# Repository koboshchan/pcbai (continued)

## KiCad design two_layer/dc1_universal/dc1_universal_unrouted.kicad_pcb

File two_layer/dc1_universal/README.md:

Universal DC1 hand-soldered card

This is one PCB design with four population variants. It replaces the repaired DC1a, DC1b, DC1c and DC1d weight cards, not DC0, DC2, DC3 or the motherboard. All existing boards remain unchanged.

The 100 × 100 mm outline, two 3.2 mm mounting holes and 76-pad straddle connector are copied from all four existing DC1 cards and mechanically checked for exact equality, including copper side, pad shape, size, position and drill. Put the L/arrow end at the motherboard socket's pin-1 end. The arrow is on both faces.

There are 532 resistor positions, all 0805 on the top face. The complete 64-input × 4-channel matrix has 256 logical weights and 512 separate positive/negative sign options. Twenty more positions cover feedback, both bias polarities and positive/negative ground balance on every channel. No weight position is omitted just because all four current models use zero there. The 112 added positions default to DNP in every current population. Existing references and positions are preserved. Future models use the same fixed 64-input/four-channel topology, supply rails and amplifier arrangement; different dimensions or circuit architectures need another board.

The left bank holds inputs 0–31 and the right bank holds inputs 32–63. Each row is an input and each bank has eight columns, positive then negative for local channels 0–3. Resistor centers have 5.2 mm column pitch and 2.65 mm row pitch. Local channels map to global neurons 0–3 on DC1a, 4–7 on DC1b, 8–11 on DC1c and 12–15 on DC1d. Connector pins A33–A36 carry local channel outputs 0–3; the motherboard slot determines the corresponding global neuron numbers. The other 72 contacts have the same roles in every variant.

Populate each board using only its matching DC1a.csv, DC1b.csv, DC1c.csv or DC1d.csv. POPULATION.md and population_chart.pdf show the same selections by physical row and column. DNP means leave the footprint empty, an open circuit. A zero weight is never a 0 Ω link. Do not populate both alternative sign positions unless the selected variant explicitly calls for them.

DC1a uses 191 resistors, DC1b 230, DC1c 181 and DC1d 141. Every variant also uses one TL074 SOIC-14, two 100 nF 50 V 0805 rail-decoupling capacitors and the manually soldered 2 × 38 straddle header. Eight resistors on each variant require 1% tolerance; the other populated resistors use the recorded 5% tolerance. CSV values and net pairs are checked against both the source boards and their physical differential-repair manifest. The source board hashes are retained in manifest.json. These selections preserve the trained network; no retraining was performed.

Routing of the 532-site board is in progress. The generated seed has zero DRC errors, 134 unconnected route items and six library-lookup warnings. No routed 532-site candidate has passed release verification yet. The previous 420-site candidate is archived outside this folder and is not a release of this design. This is a two-layer design with minimum 0.2 mm tracks, 0.2 mm clearance and 0.6/0.3 mm vias. No DRC exclusions were added. No board has been ordered or fabricated, and publication is awaiting approval.

Rebuild from this directory using /usr/bin/python3 build.py. Exported Specctra dc1_universal.dsn retains deliberately pre-routed front vertical summing buses and rear input rows, with vias connecting the input resistor pads. Complete the remaining connections with FreeRouting, save dc1_universal.ses, and run /usr/bin/python3 finish.py. Finish refuses release if any DRC error or unconnected item remains. Run population_chart.py to regenerate the solder chart.

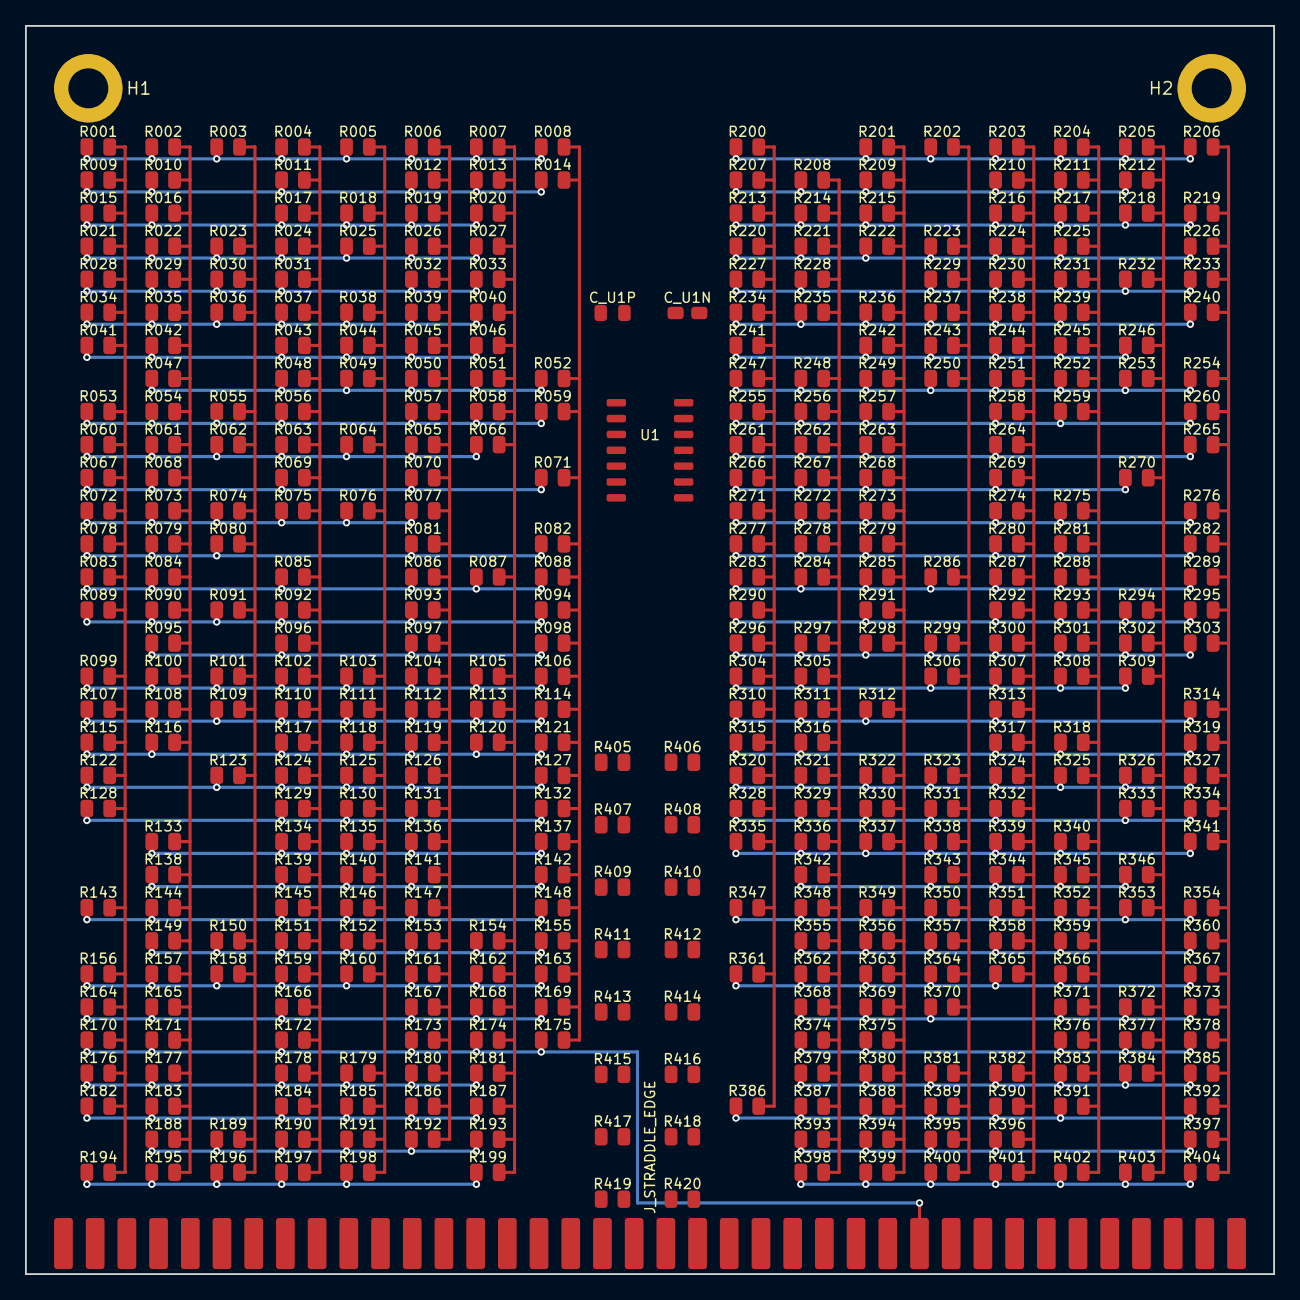
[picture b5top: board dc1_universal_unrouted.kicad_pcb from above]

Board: 2 copper layers, 100.0 x 100.0 mm, 426 parts (0 on the bottom side), 80 nets.

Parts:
C_U1N, C_U1P: 0.1uF; C_0805_2012Metric
H1, H2: MountingHole; MountingHole_3.2mm_M3_Pad
J_STRADDLE_EDGE: PinHeader_2x38_Straddle; PinHeader_2x38_Straddle_P2.54mm
R001, R002, R003, R004, R005, R006, R007, R008, R009, R010, R011, R012, R013, R014, R015, R016, R017, R018, R019, R020, R021, R022, R023, R024, R025, R026, R027, R028, R029, R030, R031, R032, R033, R034, R035, R036, R037, R038, R039, R040, R041, R042, R043, R044, R045, R046, R047, R048, R049, R050, R051, R052, R053, R054, R055, R056, R057, R058, R059, R060, R061, R062, R063, R064, R065, R066, R067, R068, R069, R070, R071, R072, R073, R074, R075, R076, R077, R078, R079, R080, R081, R082, R083, R084, R085, R086, R087, R088, R089, R090, R091, R092, R093, R094, R095, R096, R097, R098, R099, R100, R101, R102, R103, R104, R105, R106, R107, R108, R109, R110, R111, R112, R113, R114, R115, R116, R117, R118, R119, R120, R121, R122, R123, R124, R125, R126, R127, R128, R129, R130, R131, R132, R133, R134, R135, R136, R137, R138, R139, R140, R141, R142, R143, R144, R145, R146, R147, R148, R149, R150, R151, R152, R153, R154, R155, R156, R157, R158, R159, R160, R161, R162, R163, R164, R165, R166, R167, R168, R169, R170, R171, R172, R173, R174, R175, R176, R177, R178, R179, R180, R181, R182, R183, R184, R185, R186, R187, R188, R189, R190, R191, R192, R193, R194, R195, R196, R197, R198, R199, R200, R201, R202, R203, R204, R205, R206, R207, R208, R209, R210, R211, R212, R213, R214, R215, R216, R217, R218, R219, R220, R221, R222, R223, R224, R225, R226, R227, R228, R229, R230, R231, R232, R233, R234, R235, R236, R237, R238, R239, R240, R241, R242, R243, R244, R245, R246, R247, R248, R249, R250, R251, R252, R253, R254, R255, R256, R257, R258, R259, R260, R261, R262, R263, R264, R265, R266, R267, R268, R269, R270, R271, R272, R273, R274, R275, R276, R277, R278, R279, R280, R281, R282, R283, R284, R285, R286, R287, R288, R289, R290, R291, R292, R293, R294, R295, R296, R297, R298, R299, R300, R301, R302, R303, R304, R305, R306, R307, R308, R309, R310, R311, R312, R313, R314, R315, R316, R317, R318, R319, R320, R321, R322, R323, R324, R325, R326, R327, R328, R329, R330, R331, R332, R333, R334, R335, R336, R337, R338, R339, R340, R341, R342, R343, R344, R345, R346, R347, R348, R349, R350, R351, R352, R353, R354, R355, R356, R357, R358, R359, R360, R361, R362, R363, R364, R365, R366, R367, R368, R369, R370, R371, R372, R373, R374, R375, R376, R377, R378, R379, R380, R381, R382, R383, R384, R385, R386, R387, R388, R389, R390, R391, R392, R393, R394, R395, R396, R397, R398, R399, R400, R401, R402, R403, R404, R405, R406, R407, R408, R409, R410, R411, R412, R413, R414, R415, R416, R417, R418, R419, R420: POPULATION; R_0805_2012Metric
U1: TL074; SOIC-14_3.9x8.7mm_P1.27mm

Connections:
+5V_REF: J_STRADDLE_EDGE.B35, R405.1, R406.1, R407.1, R408.1, R409.1
+15V: C_U1P.2, J_STRADDLE_EDGE.B33, J_STRADDLE_EDGE.B34, U1.4
-15V: C_U1N.1, J_STRADDLE_EDGE.B37, J_STRADDLE_EDGE.B38, U1.11
GND: C_U1N.2, C_U1P.1, H1.1, H2.1, J_STRADDLE_EDGE.A37, J_STRADDLE_EDGE.A38, R410.1, R411.1, R412.1, R413.1, R414.1, R415.1, R416.1
INV_N0: R002.2, R010.2, R016.2, R022.2, R029.2, R035.2, R042.2, R047.2, R054.2, R061.2, R068.2, R073.2, R079.2, R084.2, R090.2, R095.2, R100.2, R108.2, R116.2, R133.2, R138.2, R144.2, R149.2, R157.2, R165.2, R171.2, R177.2, R183.2, R188.2, R195.2, R208.2, R214.2, R221.2, R228.2, R235.2, R248.2, R256.2, R262.2, R267.2, R272.2, R278.2, R284.2, R297.2, R305.2, R311.2, R316.2, R321.2, R329.2, R336.2, R342.2, R348.2, R355.2, R362.2, R368.2, R374.2, R379.2, R387.2, R393.2, R398.2, R405.2, R417.1, U1.2
INV_N1: R004.2, R011.2, R017.2, R024.2, R031.2, R037.2, R043.2, R048.2, R056.2, R063.2, R069.2, R075.2, R085.2, R092.2, R096.2, R102.2, R110.2, R117.2, R124.2, R129.2, R134.2, R139.2, R145.2, R151.2, R159.2, R166.2, R172.2, R178.2, R184.2, R190.2, R197.2, R202.2, R223.2, R229.2, R237.2, R243.2, R250.2, R286.2, R299.2, R306.2, R323.2, R331.2, R338.2, R343.2, R350.2, R357.2, R364.2, R370.2, R381.2, R389.2, R395.2, R400.2, R406.2, R410.2, R418.1, U1.6
INV_N2: R006.2, R012.2, R019.2, R026.2, R032.2, R039.2, R045.2, R050.2, R057.2, R065.2, R070.2, R077.2, R081.2, R086.2, R093.2, R097.2, R104.2, R112.2, R119.2, R126.2, R131.2, R136.2, R141.2, R147.2, R153.2, R161.2, R167.2, R173.2, R180.2, R186.2, R192.2, R204.2, R211.2, R217.2, R225.2, R231.2, R239.2, R245.2, R252.2, R259.2, R275.2, R281.2, R288.2, R293.2, R301.2, R308.2, R318.2, R325.2, R340.2, R345.2, R352.2, R359.2, R366.2, R371.2, R376.2, R383.2, R391.2, R402.2, R407.2, R411.2, R419.1, U1.9
INV_N3: R008.2, R014.2, R052.2, R059.2, R071.2, R082.2, R088.2, R094.2, R098.2, R106.2, R114.2, R121.2, R127.2, R132.2, R137.2, R142.2, R148.2, R155.2, R163.2, R169.2, R175.2, R206.2, R219.2, R226.2, R233.2, R240.2, R254.2, R260.2, R265.2, R276.2, R282.2, R289.2, R295.2, R303.2, R314.2, R319.2, R327.2, R334.2, R341.2, R354.2, R360.2, R367.2, R373.2, R378.2, R385.2, R392.2, R397.2, R404.2, R408.2, R412.2, R420.1, U1.13
IN_0: J_STRADDLE_EDGE.A1, R001.1, R002.1, R003.1, R004.1, R005.1, R006.1, R007.1, R008.1
IN_1: J_STRADDLE_EDGE.A2, R009.1, R010.1, R011.1, R012.1, R013.1, R014.1
IN_2: J_STRADDLE_EDGE.A3, R015.1, R016.1, R017.1, R018.1, R019.1, R020.1
IN_3: J_STRADDLE_EDGE.A4, R021.1, R022.1, R023.1, R024.1, R025.1, R026.1, R027.1
IN_4: J_STRADDLE_EDGE.A5, R028.1, R029.1, R030.1, R031.1, R032.1, R033.1
IN_5: J_STRADDLE_EDGE.A6, R034.1, R035.1, R036.1, R037.1, R038.1, R039.1, R040.1
IN_6: J_STRADDLE_EDGE.A7, R041.1, R042.1, R043.1, R044.1, R045.1, R046.1
IN_7: J_STRADDLE_EDGE.A8, R047.1, R048.1, R049.1, R050.1, R051.1, R052.1
IN_8: J_STRADDLE_EDGE.A9, R053.1, R054.1, R055.1, R056.1, R057.1, R058.1, R059.1
IN_9: J_STRADDLE_EDGE.A10, R060.1, R061.1, R062.1, R063.1, R064.1, R065.1, R066.1
IN_10: J_STRADDLE_EDGE.A11, R067.1, R068.1, R069.1, R070.1, R071.1
IN_11: J_STRADDLE_EDGE.A12, R072.1, R073.1, R074.1, R075.1, R076.1, R077.1
IN_12: J_STRADDLE_EDGE.A13, R078.1, R079.1, R080.1, R081.1, R082.1
IN_13: J_STRADDLE_EDGE.A14, R083.1, R084.1, R085.1, R086.1, R087.1, R088.1
IN_14: J_STRADDLE_EDGE.A15, R089.1, R090.1, R091.1, R092.1, R093.1, R094.1
IN_15: J_STRADDLE_EDGE.A16, R095.1, R096.1, R097.1, R098.1
IN_16: J_STRADDLE_EDGE.A17, R099.1, R100.1, R101.1, R102.1, R103.1, R104.1, R105.1, R106.1
IN_17: J_STRADDLE_EDGE.A18, R107.1, R108.1, R109.1, R110.1, R111.1, R112.1, R113.1, R114.1
IN_18: J_STRADDLE_EDGE.A19, R115.1, R116.1, R117.1, R118.1, R119.1, R120.1, R121.1
IN_19: J_STRADDLE_EDGE.A20, R122.1, R123.1, R124.1, R125.1, R126.1, R127.1
IN_20: J_STRADDLE_EDGE.A21, R128.1, R129.1, R130.1, R131.1, R132.1
IN_21: J_STRADDLE_EDGE.A22, R133.1, R134.1, R135.1, R136.1, R137.1
IN_22: J_STRADDLE_EDGE.A23, R138.1, R139.1, R140.1, R141.1, R142.1
IN_23: J_STRADDLE_EDGE.A24, R143.1, R144.1, R145.1, R146.1, R147.1, R148.1
IN_24: J_STRADDLE_EDGE.A25, R149.1, R150.1, R151.1, R152.1, R153.1, R154.1, R155.1
IN_25: J_STRADDLE_EDGE.A26, R156.1, R157.1, R158.1, R159.1, R160.1, R161.1, R162.1, R163.1
IN_26: J_STRADDLE_EDGE.A27, R164.1, R165.1, R166.1, R167.1, R168.1, R169.1
IN_27: J_STRADDLE_EDGE.A28, R170.1, R171.1, R172.1, R173.1, R174.1, R175.1
IN_28: J_STRADDLE_EDGE.A29, R176.1, R177.1, R178.1, R179.1, R180.1, R181.1
IN_29: J_STRADDLE_EDGE.A30, R182.1, R183.1, R184.1, R185.1, R186.1, R187.1
IN_30: J_STRADDLE_EDGE.A31, R188.1, R189.1, R190.1, R191.1, R192.1, R193.1
IN_31: J_STRADDLE_EDGE.A32, R194.1, R195.1, R196.1, R197.1, R198.1, R199.1
IN_32: J_STRADDLE_EDGE.B1, R200.1, R201.1, R202.1, R203.1, R204.1, R205.1, R206.1
IN_33: J_STRADDLE_EDGE.B2, R207.1, R208.1, R209.1, R210.1, R211.1, R212.1
IN_34: J_STRADDLE_EDGE.B3, R213.1, R214.1, R215.1, R216.1, R217.1, R218.1, R219.1
IN_35: J_STRADDLE_EDGE.B4, R220.1, R221.1, R222.1, R223.1, R224.1, R225.1, R226.1
IN_36: J_STRADDLE_EDGE.B5, R227.1, R228.1, R229.1, R230.1, R231.1, R232.1, R233.1
IN_37: J_STRADDLE_EDGE.B6, R234.1, R235.1, R236.1, R237.1, R238.1, R239.1, R240.1
IN_38: J_STRADDLE_EDGE.B7, R241.1, R242.1, R243.1, R244.1, R245.1, R246.1
IN_39: J_STRADDLE_EDGE.B8, R247.1, R248.1, R249.1, R250.1, R251.1, R252.1, R253.1, R254.1
IN_40: J_STRADDLE_EDGE.B9, R255.1, R256.1, R257.1, R258.1, R259.1, R260.1
IN_41: J_STRADDLE_EDGE.B10, R261.1, R262.1, R263.1, R264.1, R265.1
IN_42: J_STRADDLE_EDGE.B11, R266.1, R267.1, R268.1, R269.1, R270.1
IN_43: J_STRADDLE_EDGE.B12, R271.1, R272.1, R273.1, R274.1, R275.1, R276.1
IN_44: J_STRADDLE_EDGE.B13, R277.1, R278.1, R279.1, R280.1, R281.1, R282.1
IN_45: J_STRADDLE_EDGE.B14, R283.1, R284.1, R285.1, R286.1, R287.1, R288.1, R289.1
IN_46: J_STRADDLE_EDGE.B15, R290.1, R291.1, R292.1, R293.1, R294.1, R295.1
IN_47: J_STRADDLE_EDGE.B16, R296.1, R297.1, R298.1, R299.1, R300.1, R301.1, R302.1, R303.1
IN_48: J_STRADDLE_EDGE.B17, R304.1, R305.1, R306.1, R307.1, R308.1, R309.1
IN_49: J_STRADDLE_EDGE.B18, R310.1, R311.1, R312.1, R313.1, R314.1
IN_50: J_STRADDLE_EDGE.B19, R315.1, R316.1, R317.1, R318.1, R319.1
IN_51: J_STRADDLE_EDGE.B20, R320.1, R321.1, R322.1, R323.1, R324.1, R325.1, R326.1, R327.1
IN_52: J_STRADDLE_EDGE.B21, R328.1, R329.1, R330.1, R331.1, R332.1, R333.1, R334.1
IN_53: J_STRADDLE_EDGE.B22, R335.1, R336.1, R337.1, R338.1, R339.1, R340.1, R341.1
IN_54: J_STRADDLE_EDGE.B23, R342.1, R343.1, R344.1, R345.1, R346.1
IN_55: J_STRADDLE_EDGE.B24, R347.1, R348.1, R349.1, R350.1, R351.1, R352.1, R353.1, R354.1
IN_56: J_STRADDLE_EDGE.B25, R355.1, R356.1, R357.1, R358.1, R359.1, R360.1
IN_57: J_STRADDLE_EDGE.B26, R361.1, R362.1, R363.1, R364.1, R365.1, R366.1, R367.1
IN_58: J_STRADDLE_EDGE.B27, R368.1, R369.1, R370.1, R371.1, R372.1, R373.1
IN_59: J_STRADDLE_EDGE.B28, R374.1, R375.1, R376.1, R377.1, R378.1
IN_60: J_STRADDLE_EDGE.B29, R379.1, R380.1, R381.1, R382.1, R383.1, R384.1, R385.1
IN_61: J_STRADDLE_EDGE.B30, R386.1, R387.1, R388.1, R389.1, R390.1, R391.1, R392.1
IN_62: J_STRADDLE_EDGE.B31, R393.1, R394.1, R395.1, R396.1, R397.1
IN_63: J_STRADDLE_EDGE.B32, R398.1, R399.1, R400.1, R401.1, R402.1, R403.1, R404.1
POS_N0: R001.2, R009.2, R015.2, R021.2, R028.2, R034.2, R041.2, R053.2, R060.2, R067.2, R072.2, R078.2, R083.2, R089.2, R099.2, R107.2, R115.2, R122.2, R128.2, R143.2, R156.2, R164.2, R170.2, R176.2, R182.2, R194.2, R200.2, R207.2, R213.2, R220.2, R227.2, R234.2, R241.2, R247.2, R255.2, R261.2, R266.2, R271.2, R277.2, R283.2, R290.2, R296.2, R304.2, R310.2, R315.2, R320.2, R328.2, R335.2, R347.2, R361.2, R386.2, R413.2, U1.3
POS_N1: R003.2, R023.2, R030.2, R036.2, R055.2, R062.2, R074.2, R080.2, R091.2, R101.2, R109.2, R123.2, R150.2, R158.2, R189.2, R196.2, R201.2, R209.2, R215.2, R222.2, R236.2, R242.2, R249.2, R257.2, R263.2, R268.2, R273.2, R279.2, R285.2, R291.2, R298.2, R312.2, R322.2, R330.2, R337.2, R349.2, R356.2, R363.2, R369.2, R375.2, R380.2, R388.2, R394.2, R399.2, R414.2, U1.5
POS_N2: R005.2, R018.2, R025.2, R038.2, R044.2, R049.2, R064.2, R076.2, R103.2, R111.2, R118.2, R125.2, R130.2, R135.2, R140.2, R146.2, R152.2, R160.2, R179.2, R185.2, R191.2, R198.2, R203.2, R210.2, R216.2, R224.2, R230.2, R238.2, R244.2, R251.2, R258.2, R264.2, R269.2, R274.2, R280.2, R287.2, R292.2, R300.2, R307.2, R313.2, R317.2, R324.2, R332.2, R339.2, R344.2, R351.2, R358.2, R365.2, R382.2, R390.2, R396.2, R401.2, R409.2, R415.2, U1.10
POS_N3: R007.2, R013.2, R020.2, R027.2, R033.2, R040.2, R046.2, R051.2, R058.2, R066.2, R087.2, R105.2, R113.2, R120.2, R154.2, R162.2, R168.2, R174.2, R181.2, R187.2, R193.2, R199.2, R205.2, R212.2, R218.2, R232.2, R246.2, R253.2, R270.2, R294.2, R302.2, R309.2, R326.2, R333.2, R346.2, R353.2, R372.2, R377.2, R384.2, R403.2, R416.2, U1.12
V_SUM_0: J_STRADDLE_EDGE.A33, R417.2, U1.1
V_SUM_1: J_STRADDLE_EDGE.A34, R418.2, U1.7
V_SUM_2: J_STRADDLE_EDGE.A35, R419.2, U1.8
V_SUM_3: J_STRADDLE_EDGE.A36, R420.2, U1.14

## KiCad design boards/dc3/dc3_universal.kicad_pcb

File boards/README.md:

Current paid v2 board sources and matching fabrication ZIPs live here. PCB bytes are preserved exactly; SHA256.json records source and ZIP hashes. DC1 is the four-layer universal design. Populate four copies using DC1a.csv through DC1d.csv and POPULATION.md. ADS carrier is the current v3 targeted design.

The motherboard requires a bottom bodge wire connecting JS1 B7 at (18.25, 44.27) mm to JS2 B7 at (18.25, 55.27) mm. Fit it before powering the stack.

Only existing matching project/rule files were copied. DC2 and the motherboard final source folders did not contain matching project files. Custom footprints and 3D models are retained at the repository root. Some immutable boards embed the original /Users/lucaszhang/pcbai/3dmodels paths; on other machines provide that path as a symlink or remap models in a separate working copy. Do not edit the release sources just to change model paths.

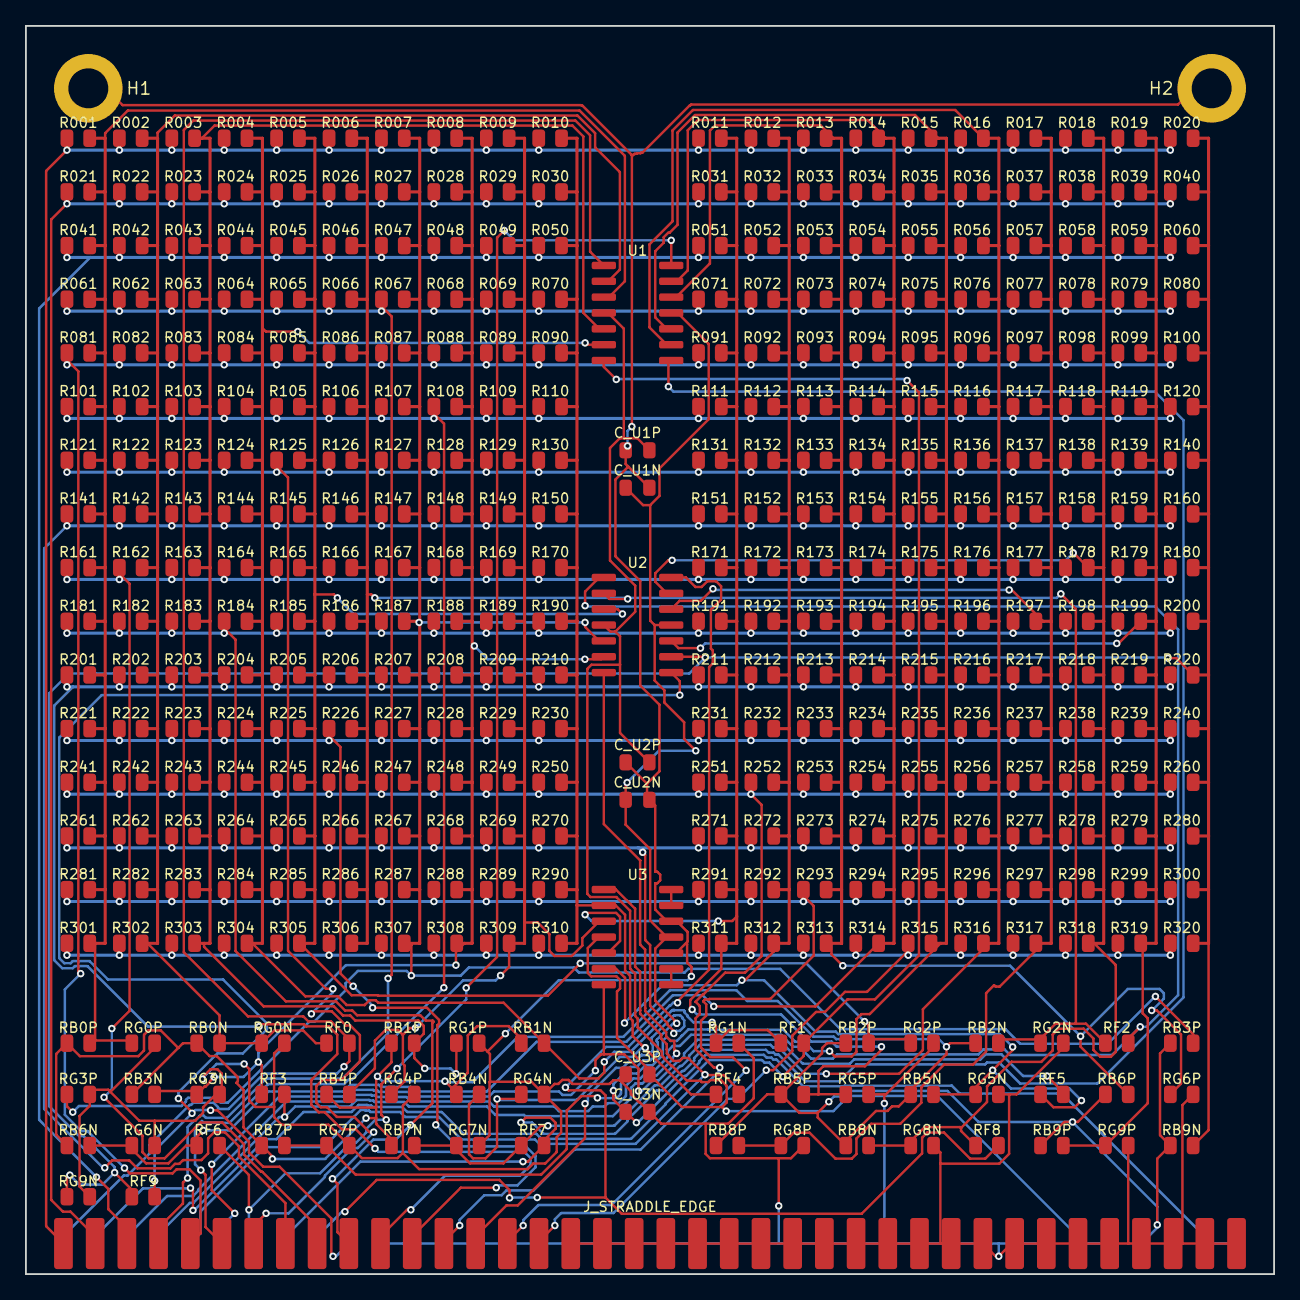
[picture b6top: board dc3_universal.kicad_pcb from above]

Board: 2 copper layers, 100.0 x 100.0 mm, 382 parts (0 on the bottom side), 52 nets.

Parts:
C_U1N, C_U1P, C_U2N, C_U2P, C_U3N, C_U3P: 0.1uF; C_0805_2012Metric
H1, H2: MountingHole; MountingHole_3.2mm_M3_Pad
J_STRADDLE_EDGE: PinHeader_2x38_Straddle; PinHeader_2x38_Straddle_P2.54mm
R001, R004, R005, R008, R009, R011, R013, R016, R017, R020, R022, R023, R024, R025, R026, R027, R029, R030, R031, R033, R034, R035, R036, R037, R038, R039, R042, R043, R045, R048, R049, R052, R053, R055, R058, R059, R060, R061, R063, R066, R068, R069, R071, R073, R076, R077, R079, R081, R084, R086, R087, R089, R092, R093, R096, R097, R099, R101, R104, R105, R108, R110, R111, R113, R115, R117, R118, R120, R121, R123, R125, R127, R128, R129, R132, R134, R135, R137, R138, R139, R141, R143, R144, R145, R148, R149, R152, R154, R155, R157, R158, R159, R162, R163, R165, R167, R169, R171, R172, R173, R176, R178, R180, R181, R184, R185, R187, R190, R192, R194, R196, R197, R199, R201, R202, R203, R206, R208, R209, R211, R213, R216, R217, R219, R221, R222, R223, R224, R225, R226, R227, R228, R230, R231, R233, R235, R236, R237, R238, R239, R240, R241, R243, R246, R247, R250, R251, R254, R255, R257, R258, R259, R261, R264, R265, R266, R267, R268, R270, R271, R273, R274, R275, R276, R277, R278, R279, R280, R281, R283, R286, R287, R288, R290, R292, R293, R296, R297, R300, R301, R302, R304, R305, R306, R307, R308, R309, R310, R311, R313, R315, R316, R317, R318, R319, R320: DNP; R_0805_2012Metric
R002, R065, R168, R183, R214: 91k; R_0805_2012Metric
R003, R062, R131, R150, R182, R284: 100k; R_0805_2012Metric
R006: 1.6M; R_0805_2012Metric
R007, R028, R109, R126, R153, R212, R218, R262, R282: 220k; R_0805_2012Metric
R010, R056, R107, R147, R174, R188, R272: 270k; R_0805_2012Metric
R012, R014, R102: 56k; R_0805_2012Metric
R015, R072: 470k; R_0805_2012Metric
R018, R040, R112, R119, R186, R189, R198, R215, R229, R234, R253: 180k; R_0805_2012Metric
R019, R046, R091, R094, R179, R252, R299: 300k; R_0805_2012Metric
R021, R047, R050, R161, R207, R232, R295, R312: 240k; R_0805_2012Metric
R032, R103: 82k; R_0805_2012Metric
R041, R220, R298: 110k; R_0805_2012Metric
R044: 51k; R_0805_2012Metric
R051, R067, R075, R314: 360k; R_0805_2012Metric
R054, R100: 430k; R_0805_2012Metric
R057: 5.1M; R_0805_2012Metric
R064, R140, R156, R200, R205, R269: 150k; R_0805_2012Metric
R070, R080, R106, R289: 130k; R_0805_2012Metric
R074, R114, R130, R146, R151, R204: 68k; R_0805_2012Metric
R078, R116, R122, R133, R166, R244, R249, R294: 200k; R_0805_2012Metric
R082, R191: 1M; R_0805_2012Metric
R083, R090, R177: 120k; R_0805_2012Metric
R085: 680k; R_0805_2012Metric
R088, R285: 750k; R_0805_2012Metric
R095, R248: 390k; R_0805_2012Metric
R098: 62k; R_0805_2012Metric
R124, R256: 43k; R_0805_2012Metric
R136, R175: 330k; R_0805_2012Metric
R142, R160: 75k; R_0805_2012Metric
R164, R260, R303: 160k; R_0805_2012Metric
R170, R193, R195: 620k; R_0805_2012Metric
R210: 33k; R_0805_2012Metric
R242: 510k; R_0805_2012Metric
R245: 1.1M; R_0805_2012Metric
R263: 820k; R_0805_2012Metric
R291: 2.7M; R_0805_2012Metric
RB0N, RB1N, RB2N, RB3P, RB4P, RB5P, RB6N, RB7N, RB8N, RB8P, RB9P: DNP; R_0805_2012Metric
RB0P: 270k; R_0805_2012Metric
RB1P, RB3N: 160k; R_0805_2012Metric
RB2P, RB4N: 560k; R_0805_2012Metric
RB5N: 2M; R_0805_2012Metric
RB6P: 240k; R_0805_2012Metric
RB7P: 3.9M; R_0805_2012Metric
RB9N: 360k; R_0805_2012Metric
RF0, RF1, RF2, RF3, RF4, RF5, RF6, RF7, RF8, RF9: 100k; R_0805_2012Metric
RG0N, RG1N, RG2N, RG3N, RG4N, RG5N, RG6N, RG7N, RG8N, RG9N: DNP; R_0805_2012Metric
RG0P: 14.7k; R_0805_2012Metric
RG1P: 24.9k; R_0805_2012Metric
RG2P: 35.7k; R_0805_2012Metric
RG3P: 61.9k; R_0805_2012Metric
RG4P: 17.4k; R_0805_2012Metric
RG5P: 28k; R_0805_2012Metric
RG6P: 14.3k; R_0805_2012Metric
RG7P: 34k; R_0805_2012Metric
RG8P: 21k; R_0805_2012Metric
RG9P: 18.2k; R_0805_2012Metric
U1, U2, U3: TL074; SOIC-14_3.9x8.7mm_P1.27mm

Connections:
+5V_REF: J_STRADDLE_EDGE.B35, RB0N.1, RB0P.1, RB1N.1, RB1P.1, RB2N.1, RB2P.1, RB3N.1, RB3P.1, RB4N.1, RB4P.1, RB5N.1, RB5P.1, RB6N.1, RB6P.1, RB7N.1, RB7P.1, RB8N.1, RB8P.1, RB9N.1, RB9P.1
+15V: C_U1P.2, C_U2P.2, C_U3P.2, J_STRADDLE_EDGE.B33, J_STRADDLE_EDGE.B34, U1.4, U2.4, U3.4
-15V: C_U1N.1, C_U2N.1, C_U3N.1, J_STRADDLE_EDGE.B37, J_STRADDLE_EDGE.B38, U1.11, U2.11, U3.11
ACT_0: J_STRADDLE_EDGE.A1, R001.1, R002.1, R003.1, R004.1, R005.1, R006.1, R007.1, R008.1, R009.1, R010.1, R011.1, R012.1, R013.1, R014.1, R015.1, R016.1, R017.1, R018.1, R019.1, R020.1
ACT_1: J_STRADDLE_EDGE.A2, R021.1, R022.1, R023.1, R024.1, R025.1, R026.1, R027.1, R028.1, R029.1, R030.1, R031.1, R032.1, R033.1, R034.1, R035.1, R036.1, R037.1, R038.1, R039.1, R040.1
ACT_2: J_STRADDLE_EDGE.A3, R041.1, R042.1, R043.1, R044.1, R045.1, R046.1, R047.1, R048.1, R049.1, R050.1, R051.1, R052.1, R053.1, R054.1, R055.1, R056.1, R057.1, R058.1, R059.1, R060.1
ACT_3: J_STRADDLE_EDGE.A4, R061.1, R062.1, R063.1, R064.1, R065.1, R066.1, R067.1, R068.1, R069.1, R070.1, R071.1, R072.1, R073.1, R074.1, R075.1, R076.1, R077.1, R078.1, R079.1, R080.1
ACT_4: J_STRADDLE_EDGE.A5, R081.1, R082.1, R083.1, R084.1, R085.1, R086.1, R087.1, R088.1, R089.1, R090.1, R091.1, R092.1, R093.1, R094.1, R095.1, R096.1, R097.1, R098.1, R099.1, R100.1
ACT_5: J_STRADDLE_EDGE.A6, R101.1, R102.1, R103.1, R104.1, R105.1, R106.1, R107.1, R108.1, R109.1, R110.1, R111.1, R112.1, R113.1, R114.1, R115.1, R116.1, R117.1, R118.1, R119.1, R120.1
ACT_6: J_STRADDLE_EDGE.A7, R121.1, R122.1, R123.1, R124.1, R125.1, R126.1, R127.1, R128.1, R129.1, R130.1, R131.1, R132.1, R133.1, R134.1, R135.1, R136.1, R137.1, R138.1, R139.1, R140.1
ACT_7: J_STRADDLE_EDGE.A8, R141.1, R142.1, R143.1, R144.1, R145.1, R146.1, R147.1, R148.1, R149.1, R150.1, R151.1, R152.1, R153.1, R154.1, R155.1, R156.1, R157.1, R158.1, R159.1, R160.1
ACT_8: J_STRADDLE_EDGE.A9, R161.1, R162.1, R163.1, R164.1, R165.1, R166.1, R167.1, R168.1, R169.1, R170.1, R171.1, R172.1, R173.1, R174.1, R175.1, R176.1, R177.1, R178.1, R179.1, R180.1
ACT_9: J_STRADDLE_EDGE.A10, R181.1, R182.1, R183.1, R184.1, R185.1, R186.1, R187.1, R188.1, R189.1, R190.1, R191.1, R192.1, R193.1, R194.1, R195.1, R196.1, R197.1, R198.1, R199.1, R200.1
ACT_10: J_STRADDLE_EDGE.A11, R201.1, R202.1, R203.1, R204.1, R205.1, R206.1, R207.1, R208.1, R209.1, R210.1, R211.1, R212.1, R213.1, R214.1, R215.1, R216.1, R217.1, R218.1, R219.1, R220.1
ACT_11: J_STRADDLE_EDGE.A12, R221.1, R222.1, R223.1, R224.1, R225.1, R226.1, R227.1, R228.1, R229.1, R230.1, R231.1, R232.1, R233.1, R234.1, R235.1, R236.1, R237.1, R238.1, R239.1, R240.1
ACT_12: J_STRADDLE_EDGE.A13, R241.1, R242.1, R243.1, R244.1, R245.1, R246.1, R247.1, R248.1, R249.1, R250.1, R251.1, R252.1, R253.1, R254.1, R255.1, R256.1, R257.1, R258.1, R259.1, R260.1
ACT_13: J_STRADDLE_EDGE.A14, R261.1, R262.1, R263.1, R264.1, R265.1, R266.1, R267.1, R268.1, R269.1, R270.1, R271.1, R272.1, R273.1, R274.1, R275.1, R276.1, R277.1, R278.1, R279.1, R280.1
ACT_14: J_STRADDLE_EDGE.A15, R281.1, R282.1, R283.1, R284.1, R285.1, R286.1, R287.1, R288.1, R289.1, R290.1, R291.1, R292.1, R293.1, R294.1, R295.1, R296.1, R297.1, R298.1, R299.1, R300.1
ACT_15: J_STRADDLE_EDGE.A16, R301.1, R302.1, R303.1, R304.1, R305.1, R306.1, R307.1, R308.1, R309.1, R310.1, R311.1, R312.1, R313.1, R314.1, R315.1, R316.1, R317.1, R318.1, R319.1, R320.1
GND: C_U1N.2, C_U1P.1, C_U2N.2, C_U2P.1, C_U3N.2, C_U3P.1, H1.1, H2.1, J_STRADDLE_EDGE.A17, J_STRADDLE_EDGE.A18, J_STRADDLE_EDGE.A19, J_STRADDLE_EDGE.A20, J_STRADDLE_EDGE.A21, J_STRADDLE_EDGE.A22, J_STRADDLE_EDGE.A23, J_STRADDLE_EDGE.A24, J_STRADDLE_EDGE.A25, J_STRADDLE_EDGE.A26, J_STRADDLE_EDGE.A27, J_STRADDLE_EDGE.A28, J_STRADDLE_EDGE.A29, J_STRADDLE_EDGE.A30, J_STRADDLE_EDGE.A31, J_STRADDLE_EDGE.A32, J_STRADDLE_EDGE.A33, J_STRADDLE_EDGE.A34, J_STRADDLE_EDGE.A35, J_STRADDLE_EDGE.A36, J_STRADDLE_EDGE.A37, J_STRADDLE_EDGE.A38, J_STRADDLE_EDGE.B11, J_STRADDLE_EDGE.B12, J_STRADDLE_EDGE.B13, J_STRADDLE_EDGE.B14, J_STRADDLE_EDGE.B15, J_STRADDLE_EDGE.B16, J_STRADDLE_EDGE.B17, J_STRADDLE_EDGE.B18, J_STRADDLE_EDGE.B19, J_STRADDLE_EDGE.B20, J_STRADDLE_EDGE.B21, J_STRADDLE_EDGE.B22, J_STRADDLE_EDGE.B23, J_STRADDLE_EDGE.B24, J_STRADDLE_EDGE.B25, J_STRADDLE_EDGE.B26, J_STRADDLE_EDGE.B27, J_STRADDLE_EDGE.B28, J_STRADDLE_EDGE.B29, J_STRADDLE_EDGE.B30, J_STRADDLE_EDGE.B31, J_STRADDLE_EDGE.B32, RG0N.2, RG0P.2, RG1N.2, RG1P.2, RG2N.2, RG2P.2, RG3N.2, RG3P.2, RG4N.2, RG4P.2, RG5N.2, RG5P.2, RG6N.2, RG6P.2, RG7N.2, RG7P.2, RG8N.2, RG8P.2, RG9N.2, RG9P.2, U3.10, U3.12
INV_L2_0: R002.2, R022.2, R042.2, R062.2, R082.2, R102.2, R122.2, R142.2, R162.2, R182.2, R202.2, R222.2, R242.2, R262.2, R282.2, R302.2, RB0N.2, RF0.1, RG0N.1, U1.2
INV_L2_1: R004.2, R024.2, R044.2, R064.2, R084.2, R104.2, R124.2, R144.2, R164.2, R184.2, R204.2, R224.2, R244.2, R264.2, R284.2, R304.2, RB1N.2, RF1.1, RG1N.1, U1.6
INV_L2_2: R006.2, R026.2, R046.2, R066.2, R086.2, R106.2, R126.2, R146.2, R166.2, R186.2, R206.2, R226.2, R246.2, R266.2, R286.2, R306.2, RB2N.2, RF2.1, RG2N.1, U2.2
INV_L2_3: R008.2, R028.2, R048.2, R068.2, R088.2, R108.2, R128.2, R148.2, R168.2, R188.2, R208.2, R228.2, R248.2, R268.2, R288.2, R308.2, RB3N.2, RF3.1, RG3N.1, U2.6
INV_L2_4: R010.2, R030.2, R050.2, R070.2, R090.2, R110.2, R130.2, R150.2, R170.2, R190.2, R210.2, R230.2, R250.2, R270.2, R290.2, R310.2, RB4N.2, RF4.1, RG4N.1, U3.2
INV_L2_5: R012.2, R032.2, R052.2, R072.2, R092.2, R112.2, R132.2, R152.2, R172.2, R192.2, R212.2, R232.2, R252.2, R272.2, R292.2, R312.2, RB5N.2, RF5.1, RG5N.1, U3.6
INV_L2_6: R014.2, R034.2, R054.2, R074.2, R094.2, R114.2, R134.2, R154.2, R174.2, R194.2, R214.2, R234.2, R254.2, R274.2, R294.2, R314.2, RB6N.2, RF6.1, RG6N.1, U1.13
INV_L2_7: R016.2, R036.2, R056.2, R076.2, R096.2, R116.2, R136.2, R156.2, R176.2, R196.2, R216.2, R236.2, R256.2, R276.2, R296.2, R316.2, RB7N.2, RF7.1, RG7N.1, U1.9
INV_L2_8: R018.2, R038.2, R058.2, R078.2, R098.2, R118.2, R138.2, R158.2, R178.2, R198.2, R218.2, R238.2, R258.2, R278.2, R298.2, R318.2, RB8N.2, RF8.1, RG8N.1, U2.13
INV_L2_9: R020.2, R040.2, R060.2, R080.2, R100.2, R120.2, R140.2, R160.2, R180.2, R200.2, R220.2, R240.2, R260.2, R280.2, R300.2, R320.2, RB9N.2, RF9.1, RG9N.1, U2.9
NC_U3_8: U3.8, U3.9
NC_U3_14: U3.13, U3.14
POS_L2_0: R001.2, R021.2, R041.2, R061.2, R081.2, R101.2, R121.2, R141.2, R161.2, R181.2, R201.2, R221.2, R241.2, R261.2, R281.2, R301.2, RB0P.2, RG0P.1, U1.3
POS_L2_1: R003.2, R023.2, R043.2, R063.2, R083.2, R103.2, R123.2, R143.2, R163.2, R183.2, R203.2, R223.2, R243.2, R263.2, R283.2, R303.2, RB1P.2, RG1P.1, U1.5
POS_L2_2: R005.2, R025.2, R045.2, R065.2, R085.2, R105.2, R125.2, R145.2, R165.2, R185.2, R205.2, R225.2, R245.2, R265.2, R285.2, R305.2, RB2P.2, RG2P.1, U2.3
POS_L2_3: R007.2, R027.2, R047.2, R067.2, R087.2, R107.2, R127.2, R147.2, R167.2, R187.2, R207.2, R227.2, R247.2, R267.2, R287.2, R307.2, RB3P.2, RG3P.1, U2.5
POS_L2_4: R009.2, R029.2, R049.2, R069.2, R089.2, R109.2, R129.2, R149.2, R169.2, R189.2, R209.2, R229.2, R249.2, R269.2, R289.2, R309.2, RB4P.2, RG4P.1, U3.3
POS_L2_5: R011.2, R031.2, R051.2, R071.2, R091.2, R111.2, R131.2, R151.2, R171.2, R191.2, R211.2, R231.2, R251.2, R271.2, R291.2, R311.2, RB5P.2, RG5P.1, U3.5
POS_L2_6: R013.2, R033.2, R053.2, R073.2, R093.2, R113.2, R133.2, R153.2, R173.2, R193.2, R213.2, R233.2, R253.2, R273.2, R293.2, R313.2, RB6P.2, RG6P.1, U1.12
POS_L2_7: R015.2, R035.2, R055.2, R075.2, R095.2, R115.2, R135.2, R155.2, R175.2, R195.2, R215.2, R235.2, R255.2, R275.2, R295.2, R315.2, RB7P.2, RG7P.1, U1.10
POS_L2_8: R017.2, R037.2, R057.2, R077.2, R097.2, R117.2, R137.2, R157.2, R177.2, R197.2, R217.2, R237.2, R257.2, R277.2, R297.2, R317.2, RB8P.2, RG8P.1, U2.12
POS_L2_9: R019.2, R039.2, R059.2, R079.2, R099.2, R119.2, R139.2, R159.2, R179.2, R199.2, R219.2, R239.2, R259.2, R279.2, R299.2, R319.2, RB9P.2, RG9P.1, U2.10
SCORE_0: J_STRADDLE_EDGE.B1, RF0.2, U1.1
SCORE_1: J_STRADDLE_EDGE.B2, RF1.2, U1.7
SCORE_2: J_STRADDLE_EDGE.B3, RF2.2, U2.1
SCORE_3: J_STRADDLE_EDGE.B4, RF3.2, U2.7
SCORE_4: J_STRADDLE_EDGE.B5, RF4.2, U3.1
SCORE_5: J_STRADDLE_EDGE.B6, RF5.2, U3.7
SCORE_6: J_STRADDLE_EDGE.B7, RF6.2, U1.14
SCORE_7: J_STRADDLE_EDGE.B8, RF7.2, U1.8
SCORE_8: J_STRADDLE_EDGE.B9, RF8.2, U2.14
SCORE_9: J_STRADDLE_EDGE.B10, RF9.2, U2.8
